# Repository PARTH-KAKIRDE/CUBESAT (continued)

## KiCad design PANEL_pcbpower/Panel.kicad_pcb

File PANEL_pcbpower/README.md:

# Panel for PCB Power: ADCS | EPS | TTC

A copy of `PANEL_jlc/` with one change: PCB Power's recommended **5 mm border on all four sides**. Neither `PANEL_jlc/` nor the board files were changed.

**Order file:** `fab/gerbers.zip` (Gerbers + drill)

## Layout

```
 ┌───────────── 5 mm frame on all four sides ────────────┐
 │  ADCS (85.2 x 84.2)   │   EPS (85.05 x 84.05)          │
 │───────────────────────┼────────────────────────────────│
 │  TTC (85.05 x 84.05)  │   (empty: TTC's SMA points     │
 │                       │    here; no tabs on this side) │
 └───────────────────────────────────────────────────────┘
```

- **Size:** 189.3 × 187.3 mm, 2 layers, 1.6 mm thick.
- **Frame:** 5 mm wide, with a 3 mm routed gap to the boards. There are no cuts in the frame corners.
- **Tabs:** 5 mm mouse-bite tabs (0.6 mm holes at 1.0 mm pitch). The two edges that face the empty slot get no tabs (the TTC's right edge with the SMA, and the EPS's bottom edge). Each board is still held on its other three edges.
- **Tooling and fiducials:** 3 × 2 mm tooling holes and 3 × 1 mm fiducials, both on the frame.
- **Silkscreen:** text is 1.0 mm in the panel copy (PCB Power's minimum character height is 1.00 mm).

## PCB Power compliance

| Rule | PCB Power | This panel |
|---|---|---|
| Track / spacing (1 oz) | 0.15 / 0.15 mm | 0.15 / 0.15 mm ✅ (at their limit) |
| Minimum via drill | 0.20 mm | 0.20 mm thermal vias (ADCS), 0.30 mm elsewhere ✅ |
| Annular ring (measured from the drill) | 0.10 mm | 0.10–0.15 mm ✅ |
| Via pad | ≥ 0.40 mm | 0.60 mm ✅ |
| Drill to drill / copper to routed edge | 0.15 / 0.20 mm | passes ✅ |
| Silkscreen | text ≥ 1.0 mm, line ≥ 0.10 mm | 1.0 / 0.17 mm ✅ |
| Maximum board | 430 × 585 mm | 189.3 × 187.3 mm ✅ |
| Gap with break routing | ≥ 2 mm | 3 mm ✅ |
| Border | 5 mm on all four sides (recommended) | 5 mm ✅ |
| Mixed designs | break routing recommended | routed gaps with mouse-bite tabs ✅ |

KiCad DRC shows the same inherited items as `PANEL_jlc/`:
- 4 flags on the TMP102 pads (0.15 mm apart, which equals PCB Power's spacing limit)
- 8 cosmetic silkscreen-overlap warnings
- courtyard and library warnings from the EPS board and KiKit's own footprints

**When ordering,** tell PCB Power the panel contains **3 different designs**.

## Regenerate

```
python3 PANEL_pcbpower/make_panel.py
kikit fab jlcpcb --no-drc PANEL_pcbpower/Panel.kicad_pcb PANEL_pcbpower/fab
```

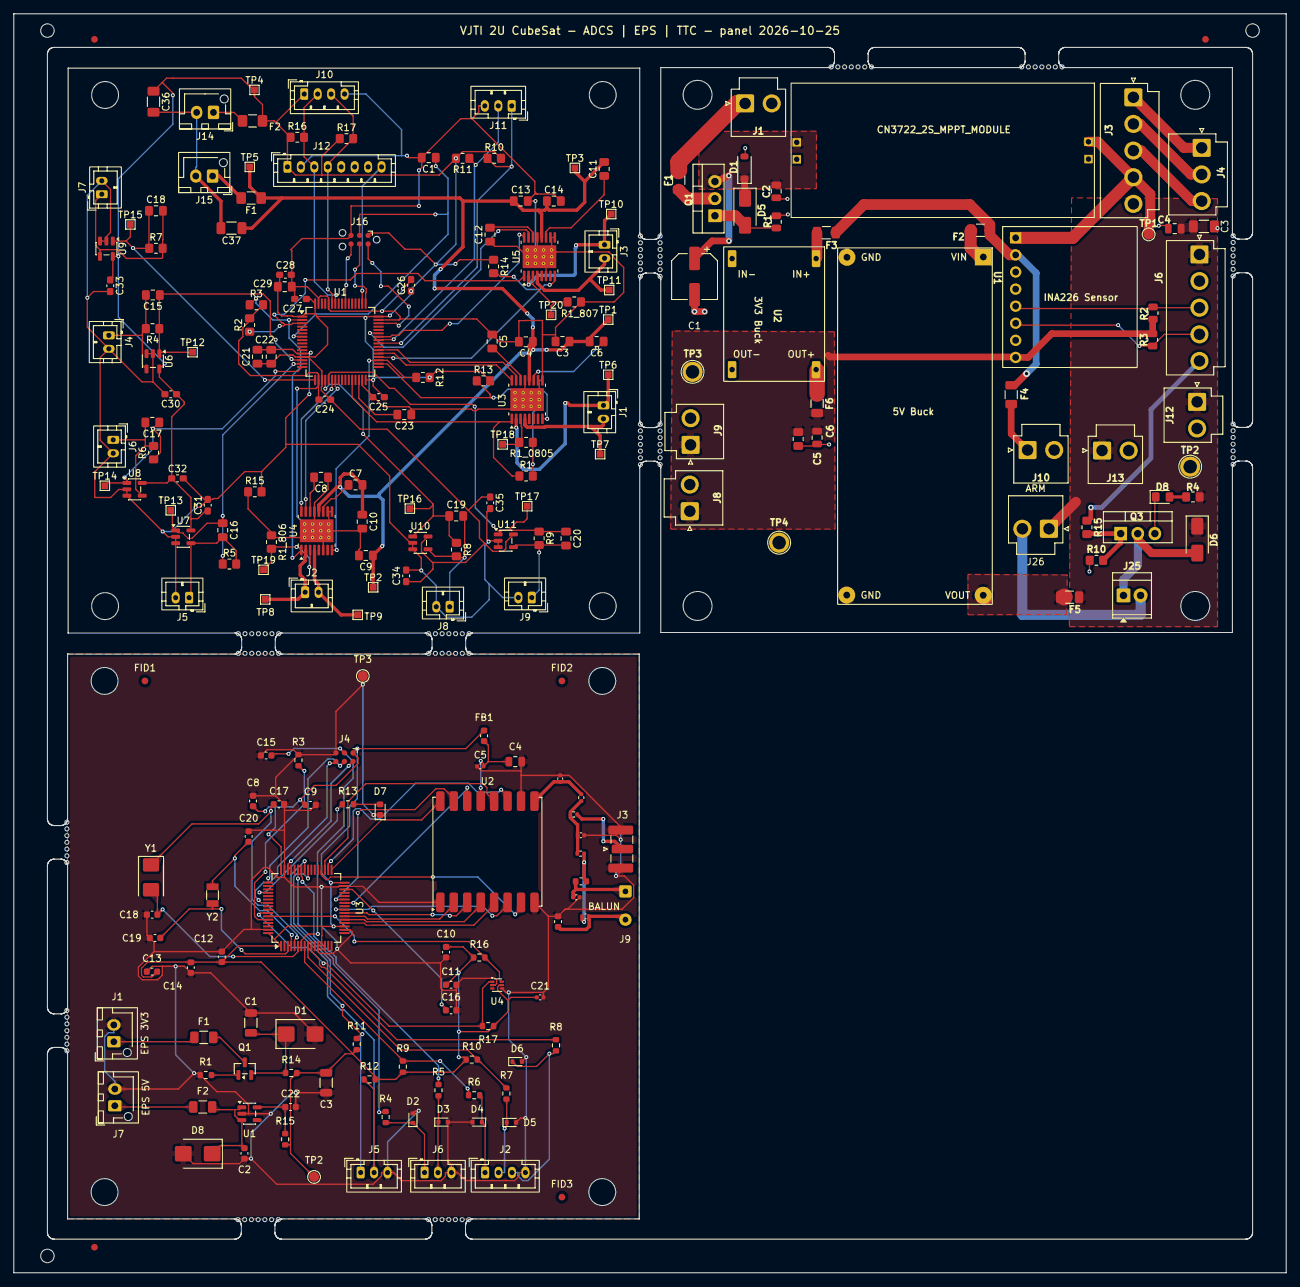
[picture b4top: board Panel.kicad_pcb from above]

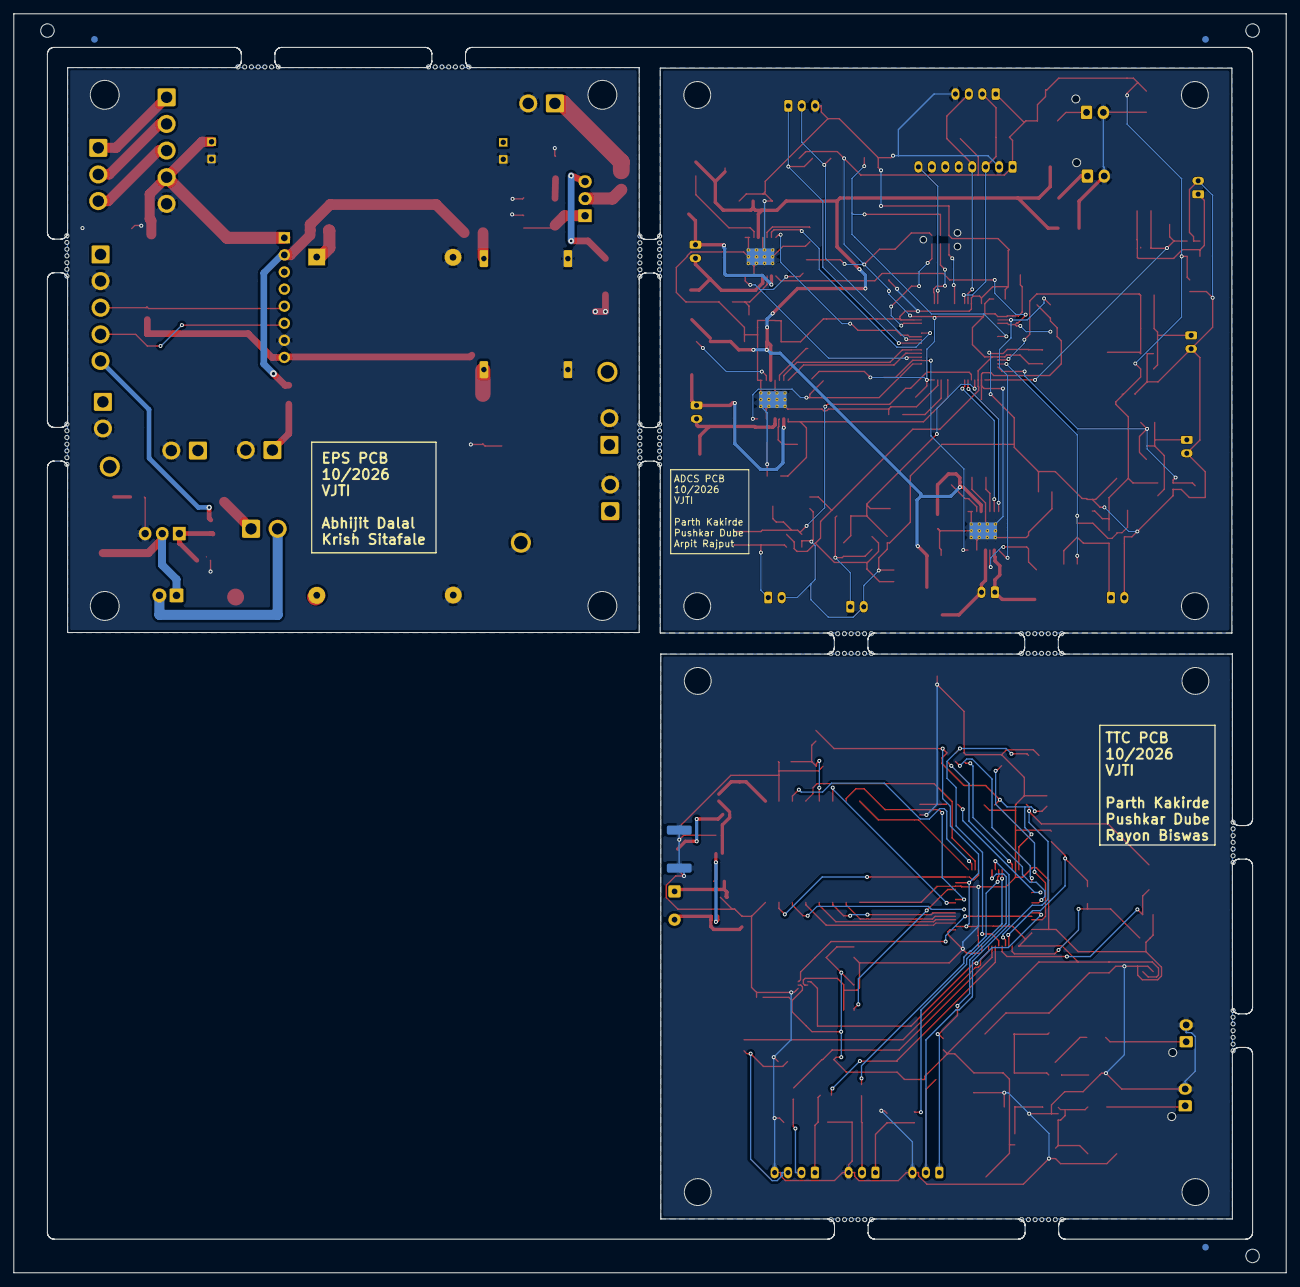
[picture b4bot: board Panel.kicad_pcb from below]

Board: 2 copper layers, 189.2 x 187.2 mm, 355 parts (3 on the bottom side), 132 nets.

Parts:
C1, C3#2: 22uF; C_1206_3216Metric
C1#2: 100uF 50V; CP_Elec_6.3x7.7
C1#3, C4#3, C10, C14: 100nF; C_0805_2012Metric_Pad1.18x1.45mm_HandSolder
C2, C13, C22#2: 1uF; C_0603_1608Metric
C2#2, C4, C6: 100nF 50V; C_0805_2012Metric
C3, C9, C13#2: 10uF; C_0805_2012Metric_Pad1.18x1.45mm_HandSolder
C3#3: 100uF 10V; C_1206_3216Metric_Pad1.33x1.80mm_HandSolder
C4#2: 10uF; C_0805_2012Metric
C5: 100uF 6.3V; C_0805_2012Metric_Pad1.18x1.45mm_HandSolder
C5#2, C8, C12#2: 2.2uF; C_0805_2012Metric_Pad1.18x1.45mm_HandSolder
C5#3, C21#2: 100nF; C_0402_1005Metric
C6#2, C7, C11#2: 0.01uF; C_0805_2012Metric_Pad1.18x1.45mm_HandSolder
C6#3, C7#2: DNP; C_0402_1005Metric
C8#2, C16: 4.7uF; C_0603_1608Metric
C9#2, C10#2, C11, C12, C14#2, C15#2: 100nF; C_0603_1608Metric
C15, C16#2, C17, C18, C19, C20#2: 22pF; C_0805_2012Metric_Pad1.18x1.45mm_HandSolder
C17#2, C18#2, C19#2, C20: CL TBD; C_0603_1608Metric
C21: 1uF; C_0805_2012Metric_Pad1.18x1.45mm_HandSolder
C22: 10nF; C_0805_2012Metric_Pad1.18x1.45mm_HandSolder
C23, C29: 4.7uF; C_0805_2012Metric_Pad1.18x1.45mm_HandSolder
C23#2, C24: 7.5pF; C_0402_1005Metric
C24#2, C25, C26, C27, C28, C30, C31, C32, C33, C34, C35: 100nF; C_0603_1608Metric_Pad1.08x0.95mm_HandSolder
C36, C37: 10uF; C_1206_3216Metric_Pad1.33x1.80mm_HandSolder
D1: TVS TODO; D_SOD-123
D1#2: SMBJ3.3A; D_SMB
D2, D3, D4, D5, D6: ESD5B5; D_SOD-523
D5#2: 12V Zener 1SMA5927; D_SMA
D6#2: SS34; D_SMA
D7: green; LED_0603_1608Metric
D8: SMBJ5.0A; D_SMB
D8#2: LED_Red; LED_0805_2012Metric_Pad1.15x1.40mm_HandSolder
F1: 2A; Fuse_1206_3216Metric_Pad1.42x1.75mm_HandSolder
F1#2, F2#2: 0.5A PTC; Fuse_1206_3216Metric
F1#3: TODO 1.5xIsc; Fuse_1206_3216Metric
F2, F5: 5A; Fuse_1206_3216Metric
F2#3: 500mA; Fuse_1206_3216Metric_Pad1.42x1.75mm_HandSolder
F3: 2.5A; Fuse_1206_3216Metric
F4: TODO max 2A; Fuse_1206_3216Metric
F6: 2A; Fuse_1206_3216Metric
FB1: BLM18PG121; L_0603_1608Metric
FID1, FID2, FID3: Fiducial; Fiducial_1mm_Mask2mm
H1, H2#3, H3#3, H4: MountingHole_4mm
H1#2, H2#2, H3#2, H4#2: M4 stack; MountingHole_4mm
H1#3, H2, H3, H4#3: MountingHole; MountingHole_4.3mm_M4
J1: EPS 3V3; JST_XH_B2B-XH-AM_1x02_P2.50mm_Vertical
J1#2, J2, J3#3, J4, J5, J6#2, J7#2, J8, J9: Conn_01x02; JST_PH_B2B-PH-K_1x02_P2.00mm_Vertical
J1#3: SOLAR_IN; JST_VH_B2P-VH_1x02_P3.96mm_Vertical
J2#2: INA226_MODULE; INA226 Current Sensor
J2#3: MISSION; JST_PH_B4B-PH-K_1x04_P2.00mm_Vertical
J3: BMS_MODULE; JST_VH_B5P-VH-B_1x05_P3.96mm_Vertical
J3#2: SMA edge; SMA_Samtec_SMA-J-P-H-ST-EM1_EdgeMount
J4#2: BATTERY_PACK; JST_VH_B3P-VH-B_1x03_P3.96mm_Vertical
J4#3: SWD TC2030; Tag-Connect_TC2030-IDC-NL_2x03_P1.27mm_Vertical
J5#2: OBC I2C; JST_PH_B3B-PH-K_1x03_P2.00mm_Vertical
J6: OBC UART; JST_PH_B3B-PH-K_1x03_P2.00mm_Vertical
J6#3: OBC_INTERFACE; JST_VH_B5P-VH_1x05_P3.96mm_Vertical
J7: EPS 5V; JST_XH_B2B-XH-AM_1x02_P2.50mm_Vertical
J8#2: ADCS_3V3_POWER; JST_VH_B2P-VH_1x02_P3.96mm_Vertical
J9#2: TTC_POWER; JST_VH_B2P-VH_1x02_P3.96mm_Vertical
J9#3: DIPOLE FEED; SolderWire-0.25sqmm_1x02_P4.2mm_D0.65mm_OD1.7mm
J10: Conn_01x04; JST_PH_B4B-PH-K_1x04_P2.00mm_Vertical
J10#2: AUX_POWER_OUT; JST_VH_B2P-VH_1x02_P3.96mm_Vertical
J11: Conn_01x03; JST_PH_B3B-PH-K_1x03_P2.00mm_Vertical
J12: ADCS_5V_A; JST_VH_B2P-VH-B_1x02_P3.96mm_Vertical
J12#2: Conn_01x08; JST_PH_B8B-PH-K_1x08_P2.00mm_Vertical
J13: ADCS_5V_B; JST_VH_B2P-VH-B_1x02_P3.96mm_Vertical
J14, J15: Conn_01x02; JST_XH_B2B-XH-AM_1x02_P2.50mm_Vertical
J16: SWD_TagConnect; Tag-Connect_TC2030-IDC-NL_2x03_P1.27mm_Vertical
J25: Pyro; TerminalBlock_TE_282834-2_1x02_P2.54mm_Horizontal
J26: PYRO_ARM; JST_VH_B2P-VH_1x02_P3.96mm_Vertical
KiKit_FID_B_1, KiKit_FID_B_2, KiKit_FID_B_3: Fiducial
KiKit_FID_T_1, KiKit_FID_T_2, KiKit_FID_T_3: Fiducial
KiKit_MB_1_1, KiKit_MB_1_2, KiKit_MB_1_3, KiKit_MB_1_4, KiKit_MB_1_5, KiKit_MB_1_6, KiKit_MB_1_7, KiKit_MB_2_1, KiKit_MB_2_2, KiKit_MB_2_3, KiKit_MB_2_4, KiKit_MB_2_5, KiKit_MB_2_6, KiKit_MB_2_7, KiKit_MB_3_1, KiKit_MB_3_2, KiKit_MB_3_3, KiKit_MB_3_4, KiKit_MB_3_5, KiKit_MB_3_6, KiKit_MB_3_7, KiKit_MB_4_1, KiKit_MB_4_2, KiKit_MB_4_3, KiKit_MB_4_4, KiKit_MB_4_5, KiKit_MB_4_6, KiKit_MB_4_7, KiKit_MB_5_1, KiKit_MB_5_2, KiKit_MB_5_3, KiKit_MB_5_4, KiKit_MB_5_5, KiKit_MB_5_6, KiKit_MB_5_7, KiKit_MB_6_1, KiKit_MB_6_2, KiKit_MB_6_3, KiKit_MB_6_4, KiKit_MB_6_5, KiKit_MB_6_6, KiKit_MB_6_7, KiKit_MB_7_1, KiKit_MB_7_2, KiKit_MB_7_3, KiKit_MB_7_4, KiKit_MB_7_5, KiKit_MB_7_6, KiKit_MB_7_7, KiKit_MB_8_1, KiKit_MB_8_2, KiKit_MB_8_3, KiKit_MB_8_4, KiKit_MB_8_5, KiKit_MB_8_6, KiKit_MB_8_7, KiKit_MB_9_1, KiKit_MB_9_2, KiKit_MB_9_3, KiKit_MB_9_4, KiKit_MB_9_5, KiKit_MB_9_6, KiKit_MB_9_7, KiKit_MB_10_1, KiKit_MB_10_2, KiKit_MB_10_3, KiKit_MB_10_4, KiKit_MB_10_5, KiKit_MB_10_6, KiKit_MB_10_7, KiKit_MB_11_1, KiKit_MB_11_2, KiKit_MB_11_3, KiKit_MB_11_4, KiKit_MB_11_5, KiKit_MB_11_6, KiKit_MB_11_7, KiKit_MB_12_1, KiKit_MB_12_2, KiKit_MB_12_3, KiKit_MB_12_4, KiKit_MB_12_5, KiKit_MB_12_6, KiKit_MB_12_7, KiKit_MB_13_1, KiKit_MB_13_2, KiKit_MB_13_3, KiKit_MB_13_4, KiKit_MB_13_5, KiKit_MB_13_6, KiKit_MB_13_7, KiKit_MB_14_1, KiKit_MB_14_2, KiKit_MB_14_3, KiKit_MB_14_4, KiKit_MB_14_5, KiKit_MB_14_6, KiKit_MB_14_7, KiKit_MB_15_1, KiKit_MB_15_2, KiKit_MB_15_3, KiKit_MB_15_4, KiKit_MB_15_5, KiKit_MB_15_6, KiKit_MB_15_7, KiKit_MB_16_1, KiKit_MB_16_2, KiKit_MB_16_3, KiKit_MB_16_4, KiKit_MB_16_5, KiKit_MB_16_6, KiKit_MB_16_7: NPTH
KiKit_TO_1, KiKit_TO_2, KiKit_TO_3: NPTH
L1, L2: 18nH; L_0603_1608Metric
Q1: IRF4905; TO-220-3_Vertical
Q1#2: AO3401A; SOT-23
Q3: IRLZ44N; TO-220-3_Vertical
R1, R3#2, R9, R10: 10k; R_0603_1608Metric
R1#2, R2#2, R3: 100k; R_0805_2012Metric_Pad1.20x1.40mm_HandSolder
R1#3: 100k; R_0805_2012Metric
R1_0805, R1_806, R1_807: 1; R_0805_2012Metric_Pad1.20x1.40mm_HandSolder
R2, R3#3: 4.7k; R_0805_2012Metric
R2#3, R18: 0R; R_0402_1005Metric
R4: 220; R_0805_2012Metric_Pad1.20x1.40mm_HandSolder
R4#2, R5#2, R6#2, R7, R8, R9#2: 680; R_0805_2012Metric_Pad1.20x1.40mm_HandSolder
R4#3, R5, R6, R7#2, R8#2, R13#2: 1k; R_0603_1608Metric
R10#2, R12, R13, R14: 10k; R_0805_2012Metric_Pad1.20x1.40mm_HandSolder
R10#3, R11, R16, R17: 4.7k; R_0805_2012Metric_Pad1.20x1.40mm_HandSolder
R11#2, R12#2, R16#2, R17#2: 4.7k; R_0603_1608Metric
R14#2: 0R; R_0603_1608Metric
R15: 0R DNP; R_0603_1608Metric
R15#2: 100; R_0805_2012Metric_Pad1.20x1.40mm_HandSolder
R15#3: 0R; R_0805_2012Metric_Pad1.20x1.40mm_HandSolder
R19: 0R DNP; R_0402_1005Metric
TP1: VBUS_TEST; TestPoint_Pad_D1.5mm
TP1#2, TP2, TP3#2, TP4, TP5, TP6, TP7, TP8, TP9, TP10, TP11, TP12, TP13, TP14, TP15, TP16, TP17, TP18, TP19, TP20: TestPoint; TestPoint_Pad_1.0x1.0mm
TP2#2: +3V3; TestPoint_Pad_D1.5mm
TP2#3: +5V_TEST; TestPoint_Plated_Hole_D2.0mm
TP3: +3V3_TEST; TestPoint_Plated_Hole_D2.0mm
TP3#3: GND; TestPoint_Pad_D1.5mm
TP4#2: GND_TEST; TestPoint_Plated_Hole_D2.0mm
U1: XL4015; XL4015 Buck
U1#2: STM32F446RETx; LQFP-64_10x10mm_P0.5mm
U1#3: TPS7A2033PDBVR; SOT-23-5
U2: MP1584 Buck Converter; MP1584 module 20mm_15mm
U2#2: RFM98W-433S2; HOPERF_RFM9XW_SMD
U3: CN3722_2S_MPPT_MODULE; MPPT Solar
U3#2: STM32F446RET6; LQFP-64_10x10mm_P0.5mm
U3#3: DRV8833PWP_X; HTSSOP-16-1EP_4.4x5mm_P0.65mm_EP3.4x5mm_Mask2.46x2.31mm_The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
U4: DRV8833PWP_Y; HTSSOP-16-1EP_4.4x5mm_P0.65mm_EP3.4x5mm_Mask2.46x2.31mm_The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
U4#2: TMP102; SOT-563
U5: DRV8833PWP_Z; HTSSOP-16-1EP_4.4x5mm_P0.65mm_EP3.4x5mm_Mask2.46x2.31mm_The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
U6, U7, U8, U9, U10, U11: MCP6001-OT; SOT-23-5
Y1: 8MHz; Crystal_SMD_5032-2Pin_5.0x3.2mm
Y2: 32.768kHz; Crystal_SMD_3215-2Pin_3.2x1.5mm

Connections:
ADCS-/3.3V: C21.1, C22.1, C24#2.1, C25.1, C26.1, C27.1, C28.1, C29.1, C30.1, C31.1, C32.1, C33.1, C34.1, C35.1, C36.1, F2#3.1, J10.1, J12#2.1, J16.1 (VCC), R10#3.2, R11.2, R12.2, R13.2, R14.1, R16.1, R17.1, TP4.1 (1_1), U1#2.1 (VBAT), U1#2.13 (VDDA), U1#2.19 (VDD), U1#2.32 (VDD), U1#2.48 (VDD), U1#2.64 (VDD), U6.5 (V+), U7.5 (V+), U8.5 (V+), U9.5 (V+), U10.5 (V+), U11.5 (V+)
ADCS-/5V: C3.1, C4#3.1, C6#2.2, C7.2, C9.1, C10.1, C11#2.2, C13#2.1, C14.1, C37.1, F1.1, TP1#2.1 (1_1), TP2.1 (1_1), TP3#2.1 (1_1), TP5.1 (1_1), U3#3.12 (VM), U4.12 (VM), U5.12 (VM)
ADCS-/DRVX_AIN1: U1#2.37 (TIM8_CH1), U3#3.16 (AIN1)
ADCS-/DRVX_AIN2: U1#2.38 (TIM8_CH2), U3#3.15 (AIN2)
ADCS-/DRVX_FAULT: R13.1, U1#2.34 (PB13), U3#3.8 (~FAULT)
ADCS-/DRVX_SLEEP: R1#2.1, U1#2.28 (PB2), U3#3.1 (~SLEEP)
ADCS-/DRVY_AIN1: U1#2.22 (TIM3_CH1), U4.16 (AIN1)
ADCS-/DRVY_AIN2: U1#2.23 (TIM3_CH2), U4.15 (AIN2)
ADCS-/DRVY_FAULT: R12.1, U1#2.35 (PB14), U4.8 (~FAULT)
ADCS-/DRVY_SLEEP: R3.1, U1#2.2 (PC13), U4.1 (~SLEEP)
ADCS-/DRVZ_AIN1: U1#2.42 (TIM1_CH2), U5.16 (AIN1)
ADCS-/DRVZ_AIN2: U1#2.43 (TIM1_CH3), U5.15 (AIN2)
ADCS-/DRVZ_FAULT: R14.2, U1#2.36 (PB15), U5.8 (~FAULT)
ADCS-/DRVZ_SLEEP: R2#2.1, U1#2.3 (PC14), U5.1 (~SLEEP)
ADCS-/I2C1_SCL: J10.2, J12#2.3, R16.2, U1#2.58 (PB6)
ADCS-/I2C1_SDA: J10.3, J12#2.4, R17.2, U1#2.59 (PB7)
ADCS-/MPU_INT: J12#2.8, U1#2.50 (PA15)
ADCS-/NRST: C1#3.1, J16.3 (~RESET), U1#2.7 (NRST)
ADCS-/RPI_SCL: J11.2, R11.1, U1#2.41 (PA8)
ADCS-/RPI_SDA: J11.1, R10#3.1, U1#2.40 (PC9)
ADCS-/SS1: C15.1, R4#2.1, TP12.1 (1_1), U1#2.14 (PA0), U6.1
ADCS-/SS2: C16#2.1, R5#2.1, TP13.1 (1_1), U1#2.15 (PA1), U7.1
ADCS-/SS3: C17.1, R6#2.1, TP14.1 (1_1), U1#2.16 (PA2), U8.1
ADCS-/SS4: C18.1, R7.1, TP15.1 (1_1), U1#2.17 (PA3), U9.1
ADCS-/SS5: C19.1, R8.1, TP16.1 (1_1), U1#2.20 (PA4), U10.1
ADCS-/SS6: C20#2.1, R9#2.1, TP17.1 (1_1), U1#2.21 (PA5), U11.1
ADCS-/SWDCLK: J16.4 (SWCLK), U1#2.49 (PA14)
ADCS-/SWDIO: J16.2 (SWDIO), U1#2.46 (PA13)
ADCS-/SWO: J16.6 (SWO), U1#2.55 (PB3)
ADCS-/X_AISEN: R1_0805.2, TP18.1 (1_1), U3#3.3 (AISEN)
ADCS-/X_AOUT1: J1#2.1, TP6.1 (1_1), U3#3.2 (AOUT1)
ADCS-/X_AOUT2: J1#2.2, TP7.1 (1_1), U3#3.4 (AOUT2)
ADCS-/Y_AISEN: R1_806.2, TP19.1 (1_1), U4.3 (AISEN)
ADCS-/Y_AOUT1: J2.1, TP8.1 (1_1), U4.2 (AOUT1)
ADCS-/Y_AOUT2: J2.2, TP9.1 (1_1), U4.4 (AOUT2)
ADCS-/Z_AISEN: R1_807.2, TP20.1 (1_1), U5.3 (AISEN)
ADCS-/Z_AOUT1: J3#3.1, TP10.1 (1_1), U5.2 (AOUT1)
ADCS-/Z_AOUT2: J3#3.2, TP11.1 (1_1), U5.4 (AOUT2)
ADCS-GND: C1#3.2, C3.2, C4#3.2, C5#2.1, C8.1, C9.2, C10.2, C12#2.1, C13#2.2, C14.2, C23.1, C24#2.2, C25.2, C26.2, C27.2, C28.2, C29.2, C36.2, C37.2, J10.4, J11.3, J12#2.2, J14.2, J15.2, J16.5 (GND), R1#2.2, R1_0805.1, R1_806.1, R1_807.1, R2#2.2, R3.2, R15#3.1, U1#2.18 (VSS), U1#2.31 (VSS), U1#2.47 (VSS), U1#2.60 (BOOT0), U1#2.63 (VSS), U3#3.6 (BISEN), U3#3.9 (BIN1), U3#3.10 (BIN2), U3#3.13 (GND), U3#3.17 (GND), U4.6 (BISEN), U4.9 (BIN1), U4.10 (BIN2), U4.13 (GND), U4.17 (GND), U5.6 (BISEN), U5.9 (BIN1), U5.10 (BIN2), U5.13 (GND), U5.17 (GND)
ADCS-GNDA: C21.2, C22.2, C30.2, C31.2, C32.2, C33.2, C34.2, C35.2, J4.2, J5.2, J6#2.2, J7#2.2, J8.2, J9.2, R15#3.2, U1#2.12 (VSSA), U6.2 (V-), U6.3 (+), U7.2 (V-), U7.3 (+), U8.2 (V-), U8.3 (+), U9.2 (V-), U9.3 (+), U10.2 (V-), U10.3 (+), U11.2 (V-), U11.3 (+)
ADCS-Net-(J4-Pin_1): C15.2, J4.1, R4#2.2, U6.4 (-)
ADCS-Net-(J5-Pin_1): C16#2.2, J5.1, R5#2.2, U7.4 (-)
ADCS-Net-(J6-Pin_1): C17.2, J6#2.1, R6#2.2, U8.4 (-)
ADCS-Net-(J7-Pin_1): C18.2, J7#2.1, R7.2, U9.4 (-)
ADCS-Net-(J8-Pin_1): C19.2, J8.1, R8.2, U10.4 (-)
ADCS-Net-(J9-Pin_1): C20#2.2, J9.1, R9#2.2, U11.4 (-)
ADCS-Net-(J14-Pin_1): F2#3.2, J14.1
ADCS-Net-(J15-Pin_1): F1.2, J15.1
ADCS-Net-(U1-VCAP_1): C23.2, U1#2.30 (VCAP_1)
ADCS-Net-(U3-VCP): C6#2.1, U3#3.11 (VCP)
ADCS-Net-(U3-VINT): C5#2.2, U3#3.14 (VINT)
ADCS-Net-(U4-VCP): C7.1, U4.11 (VCP)
ADCS-Net-(U4-VINT): C8.2, U4.14 (VINT)
ADCS-Net-(U5-VCP): C11#2.1, U5.11 (VCP)
ADCS-Net-(U5-VINT): C12#2.2, U5.14 (VINT)
EPS-/+3V3: C5.1, C6.1, F6.2, J2#2.8, J8#2.1, J9#2.1, R2.1, R3#3.1, TP3.1 (1_1)
EPS-/+5V: C3#3.1, C4.1, D6#2.1 (K), F5.1, J6#3.1, J12.1, J13.1, J26.1, R4.1, TP2#3.1 (1_1)
EPS-/BATT+: J3.1, J4#2.1
EPS-/BATT-: J3.3, J4#2.3
EPS-/BATT_MID: J3.2, J4#2.2
EPS-/DRAIN: D6#2.2 (A), J25.1, Q3.2 (D)
EPS-/GATE: Q3.1 (G), R10#2.2, R15#2.2
EPS-/MPPT_IN+: C1#2.1, C2#2.1, D1.1 (A1), D5#2.1 (K), Q1.3 (S), U3.1 (Vin)
EPS-/PYRO_ARMED: J25.2, J26.2
EPS-/PYRO_FIRE: J6#3.5, R15#2.1
EPS-/SCL: J2#2.6, J6#3.4, R3#3.2
EPS-/SDA: J2#2.5, J6#3.3, R2.2
EPS-/VBUS: J2#2.1, J3.4, TP1.1 (1_1), U3.4 (Vout)
EPS-/VBUS_DIST: F2.2, F3.1, F4.1, J2#2.2
EPS-GND: C1#2.2, C2#2.2, C3#3.2, C4.2, C5.2, C6.2, D1.2 (A2), D8#2.1 (K), J1#3.2, J2#2.7, J3.5, J6#3.2, J8#2.2, J9#2.2, J10#2.2, J12.2, J13.2, Q3.3 (S), R1#3.1, R10#2.1, TP4#2.1 (1_1), U1.2 (GND), U1.3 (GND), U2.2 (IN-), U2.4 (OUT-), U3.2 (GND), U3.3 (GND)
EPS-Net-(D5-A): D5#2.2 (A), Q1.1 (G), R1#3.2
EPS-Net-(D8-A): D8#2.2 (A), R4.2
EPS-Net-(J1-Pin_1): F1#3.1, J1#3.1
EPS-Net-(J10-Pin_1): F4.2, J10#2.1
EPS-Net-(Q1-D): F1#3.2, Q1.2 (D)
EPS-Net-(U1-Vin): F2.1, U1.1 (Vin)
EPS-Net-(U1-Vout): F5.2, U1.4 (Vout)
EPS-Net-(U2-IN+): F3.2, U2.1 (IN+)
EPS-Net-(U2-OUT+): F6.1, U2.3 (OUT+)
TTC-+3V3: C3#2.1, C8#2.1, C9#2.1, C10#2.1, C11.1, C12.1, C13.1, C14#2.1, C21#2.1, FB1.1, J4#3.1, R9.1, R10.1, R11#2.1, R12#2.2, R14#2.2, R15.2, R16#2.1, R17#2.2, TP2#2.1, U3#2.1, U3#2.13, U3#2.19, U3#2.32, U3#2.48, U3#2.64, U4#2.5
TTC-/BURN_EN: R8#2.2, U3#2.10
TTC-/DEPLOY_SW: R6.2, R9.2, U3#2.8
TTC-/I2C_SCL: R17#2.1, U3#2.58, U4#2.1
TTC-/I2C_SDA: R16#2.2, U3#2.59, U4#2.6
TTC-/NRST: C15#2.2, J4#3.3, U3#2.7
TTC-/OBC_SCL: J5#2.2, R12#2.1, U3#2.41
TTC-/OBC_SDA: J5#2.1, R11#2.2, U3#2.40
TTC-/RBF_IN: R7#2.2, R10.2, U3#2.9
TTC-/RFM_DIO0: U2#2.14, U3#2.26
TTC-/RFM_DIO1: U2#2.15, U3#2.27
TTC-/RFM_DIO2: U2#2.16, U3#2.33
TTC-/RFM_DIO3: U2#2.11, U3#2.34
TTC-/RFM_DIO4: U2#2.12, U3#2.35
TTC-/RFM_DIO5: U2#2.7, U3#2.36
TTC-/RFM_NSS: U2#2.5, U3#2.20
TTC-/RFM_RESET: U2#2.6, U3#2.24
TTC-/SPI1_MISO: U2#2.2, U3#2.22
TTC-/SPI1_MOSI: U2#2.3, U3#2.23
TTC-/SPI1_SCK: U2#2.4, U3#2.21
TTC-/SWCLK: J4#3.4, U3#2.49
TTC-/SWDIO: J4#3.2, U3#2.46
TTC-/SWO: J4#3.6, U3#2.55
TTC-/UART_RX: R4#3.2, U3#2.43
TTC-/UART_TX: R5.2, U3#2.42
TTC-GND: C1.2, C2.2, C3#2.2, C4#2.2, C5#3.2, C6#3.2, C7#2.2, C8#2.2, C9#2.2, C10#2.2, C11.2, C12.2, C13.2, C14#2.2, C15#2.1, C16.2, C17#2.1, C18#2.1, C19#2.1, C20.1, C21#2.2, C22#2.2, C23#2.2, D1#2.2, D2.2, D3.2, D4.2, D5.2, D6.2, D7.1, D8.2, J1.2, J2#3.4, J3#2.2, J4#3.5, J5#2.3, J6.3, J7.2, L2.2, R1.2, R3#2.1, TP3#3.1, U1#3.2, U2#2.1, U2#2.8, U2#2.10, U3#2.12, U3#2.18, U3#2.31, U3#2.47, U3#2.63, U4#2.2, U4#2.4
TTC-Net-(C7-Pad1): C7#2.1, R2#3.2, R18.1, R19.1
TTC-Net-(C24-Pad1): C24.1, L1.1, R19.2
TTC-Net-(D1-K): C1.1, D1#2.1, Q1#2.2, R14#2.1
TTC-Net-(D2-A1): D2.1, J6.1, R4#3.1
TTC-Net-(D3-A1): D3.1, J6.2, R5.1
TTC-Net-(D4-A1): D4.1, J2#3.1, R6.1
TTC-Net-(D5-A1): D5.1, J2#3.2, R7#2.1
TTC-Net-(D6-A1): D6.1, J2#3.3, R8#2.1
TTC-Net-(D7-A): D7.2, R13#2.1
TTC-Net-(D8-K): C2.1, D8.1, F2#2.2, U1#3.1, U1#3.3
TTC-Net-(J1-Pin_1): F1#2.1, J1.1
TTC-Net-(J3-In): J3#2.1, R18.2
TTC-Net-(J7-Pin_1): F2#2.1, J7.1
TTC-Net-(J9-Pin_1): C23#2.1, J9#3.1, L1.2
TTC-Net-(J9-Pin_2): C24.2, J9#3.2, L2.1
TTC-Net-(Q1-D): F1#2.2, Q1#2.3
TTC-Net-(Q1-G): Q1#2.1, R1.1
TTC-Net-(U1-VOUT): C22#2.1, R15.1, U1#3.5
TTC-Net-(U2-3.3V): C4#2.1, C5#3.1, FB1.2, U2#2.13
TTC-Net-(U2-ANT): C6#3.1, R2#3.1, U2#2.9
TTC-Net-(U3-BOOT0): R3#2.2, U3#2.60
TTC-Net-(U3-PC11): R13#2.2, U3#2.52
TTC-Net-(U3-PC14): C19#2.2, U3#2.3, Y2.1
TTC-Net-(U3-PC15): C20.2, U3#2.4, Y2.2
TTC-Net-(U3-PH0): C17#2.2, U3#2.5, Y1.1
TTC-Net-(U3-PH1): C18#2.2, U3#2.6, Y1.2
TTC-Net-(U3-VCAP_1): C16.1, U3#2.30
